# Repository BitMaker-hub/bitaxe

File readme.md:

# The Nerdaxe
NerdAxe is a fork from bitaxe with fullcolor display graphics. NerdAxe is indented to be an upgrade board for these who have a NerdMiner and would like to have more powerful mining features without losing the NerdMiner essence. That's why NerdAxe is currently controlled by the common board used on Nerdminer project called TTGO-TDisplayS3.

Currently exists two variants sepparated in two branches:
- **Nerdaxe Gamma**: 1,2Th with a single chip BM1370. [Nerdaxe Gamma](https://github.com/BitMaker-hub/NerdAxe/tree/gamma-1%2C2Ths)
- **Nerdaxe Ultra**: 0,5Th with a single chip BM1366. [Nerdaxe Ultra](https://github.com/BitMaker-hub/NerdAxe/tree/ultra-500Ghs)

The following fork could not be possible without the previous work of @skot, @ben & bitaxe devs. [Check bitaxe project](https://bitaxe.org)

Upgrade your NerdMiner experience throught this addon board and start playing with ASICs

## Goals
- **Plug&Play**: your NerdMiner board and convert it into a NerdAxe.
- **Standalone**: can mine directly to your pool over WiFi. No External computer needed.
- **Embedded**: low cost, low maintenance, high availability, high reliability, low power.
- **ASIC**: working with most efficient ASIC chips from Bitmain - BM1370.
- **Versatile**: solo/pool mining, autotune power/heat/efficiency.
- **Open Source**: All design files are provided.

## Features
- **TTGO-TDisplay** ESP32s3 wifi microcontroller display board
- **Multiple Screens** to allow you see all the miner stats 
- **TI TPS546D** buck regulator steps down the 5V input to power the BM1370
- **Microchip EMC2101** PWM controls the fan and monitors tach output. Measuring internal die temp isn't working.

## Software & Firmware
Nerdaxe firmware was forked from original ESP-Miner version and adapted to use TTGO board and LVGL as graphic interface lib. 
Check it here -> [ESP-Miner Nerdaxe version](https://github.com/BitMaker-hub/ESP-Miner-NerdAxe)

**Today** Nerdaxe is using the latest evolution of this firmware modified by @pmaxuw (creator of the NerdQaxe) and used for other multiple boards
Current firmware -> [ESP-Miner Nerd\*axe version](https://github.com/shufps/ESP-Miner-NerdQAxePlus)

Flash the latest Nerdaxe firmware here: 
- Go to flasher online tool: https://flasher.bitronics.store/ (recommend via Google Chrome incognito mode)
- Nerd\*axe flasher online tool: https://shufps.github.io/nerdqaxe-web-flasher/  

## The DIY area

### Asic BM1370
- The BM1370 is a undocumented SHA256 mining ASIC from Bitmain. It's mostly used in the Antminer S21pro/S21+
- Bitmain claims the BM1370 has 0.021J/GH efficiency
- The BM1370 is available (new) for around $60 each in small quantities.
- The BM1370 has a different footprint and pinout from the MB1366, BM1368 in previous bitaxe.

### Other components & build troubleshooting
- BM1370 from NBTC on AliExpress
- [40x40mm heatsink and 5V fan](https://www.aliexpress.com/item/2251832861666365.html) from a random AliExpress seller. At least half of these arrived broken in some way. But they are cheap and the working ones do keep the BM1387's nice and cool when used with some thermal compound.
    - Swap this fan with the [Noctua NF-A4x10](https://noctua.at/en/products/fan/nf-a4x10-pwm) 5V 4-Pin fan for a much more pleasant experience.
- Board is designed with [KiCad 8](https://www.kicad.org) design files
- All of the parts on the board are listed in the KiCad BOM
- Check out [building.md](building.md) for PCB ordering tips
- Check out [assembly.md](assembly.md) for assembly tips

### Power Supply Requirements
- 5VDC Power supply 5A minimum. Should be capable of over 25W

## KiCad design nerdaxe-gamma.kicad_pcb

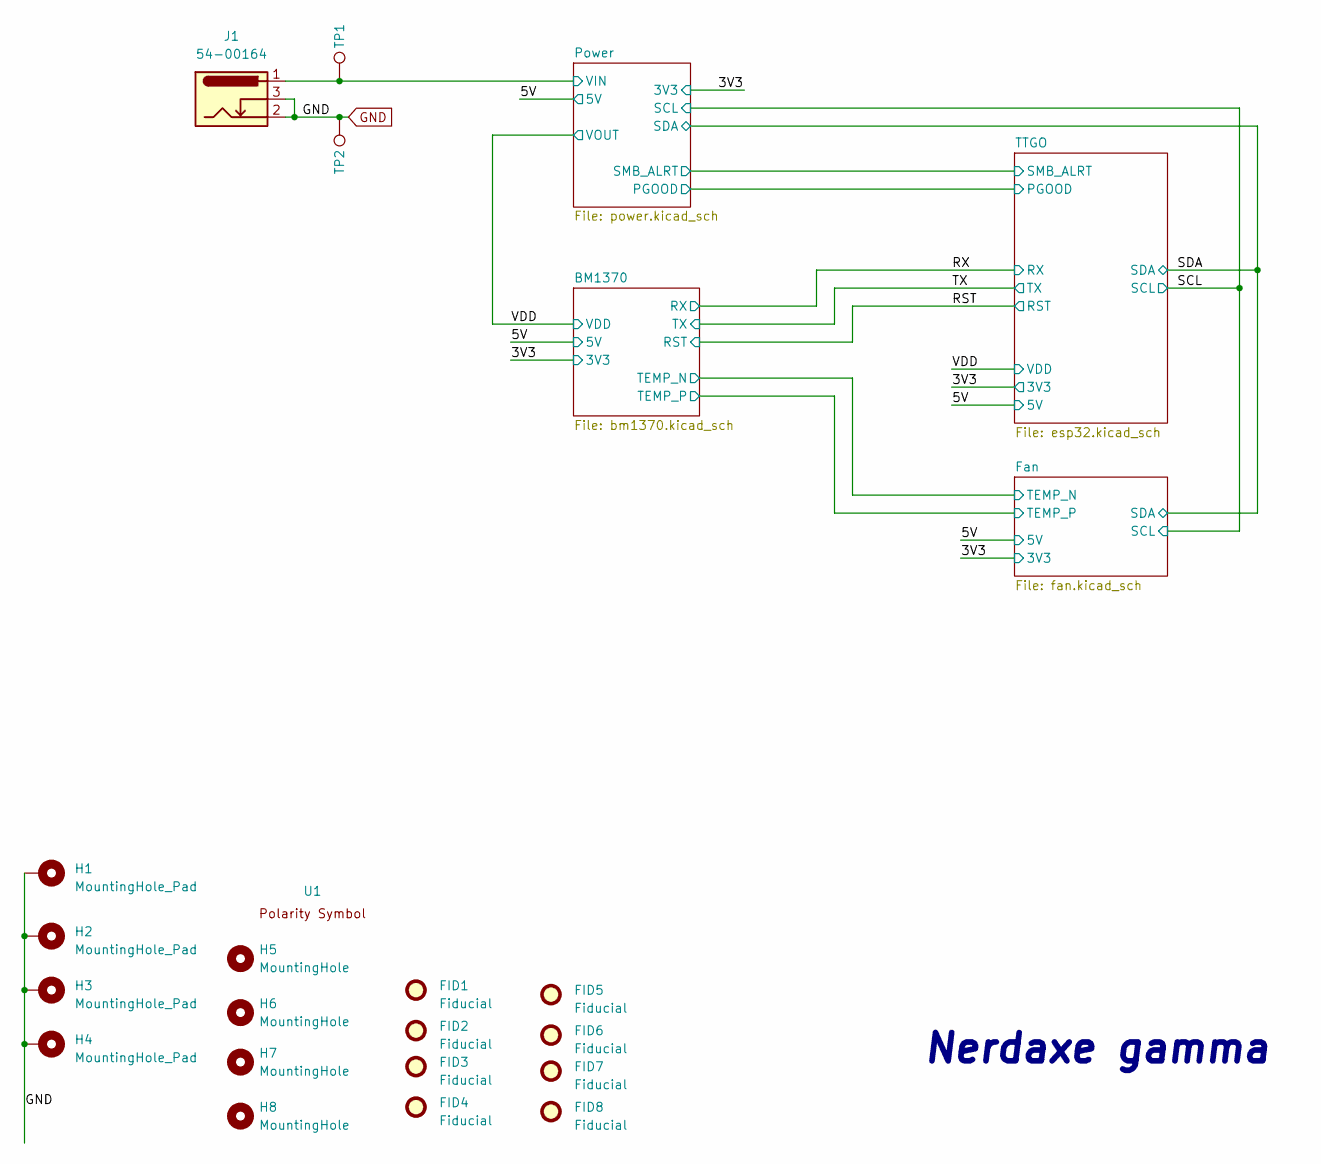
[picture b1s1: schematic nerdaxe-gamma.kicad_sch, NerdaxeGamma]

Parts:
FID1, FID2, FID3, FID4, FID5, FID6, FID7, FID8: Fiducial; Fiducial_1mm_Mask2mm
H1, H2, H3, H4: MountingHole_Pad; MountingHole_3mm_Pad_Via
H5, H6, H7, H8: MountingHole; MountingHole_3.5mm
J1: 54-00164; TENSILITY_54-00164; PARTNO 54-00164; LCSC C431534
TP1, TP2: TestPoint; TestPoint_Pad_D1.5mm
U1: polarity

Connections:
/5V: J1.1, TP1.1; also elsewhere on the board

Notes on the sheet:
Nerdaxe gamma

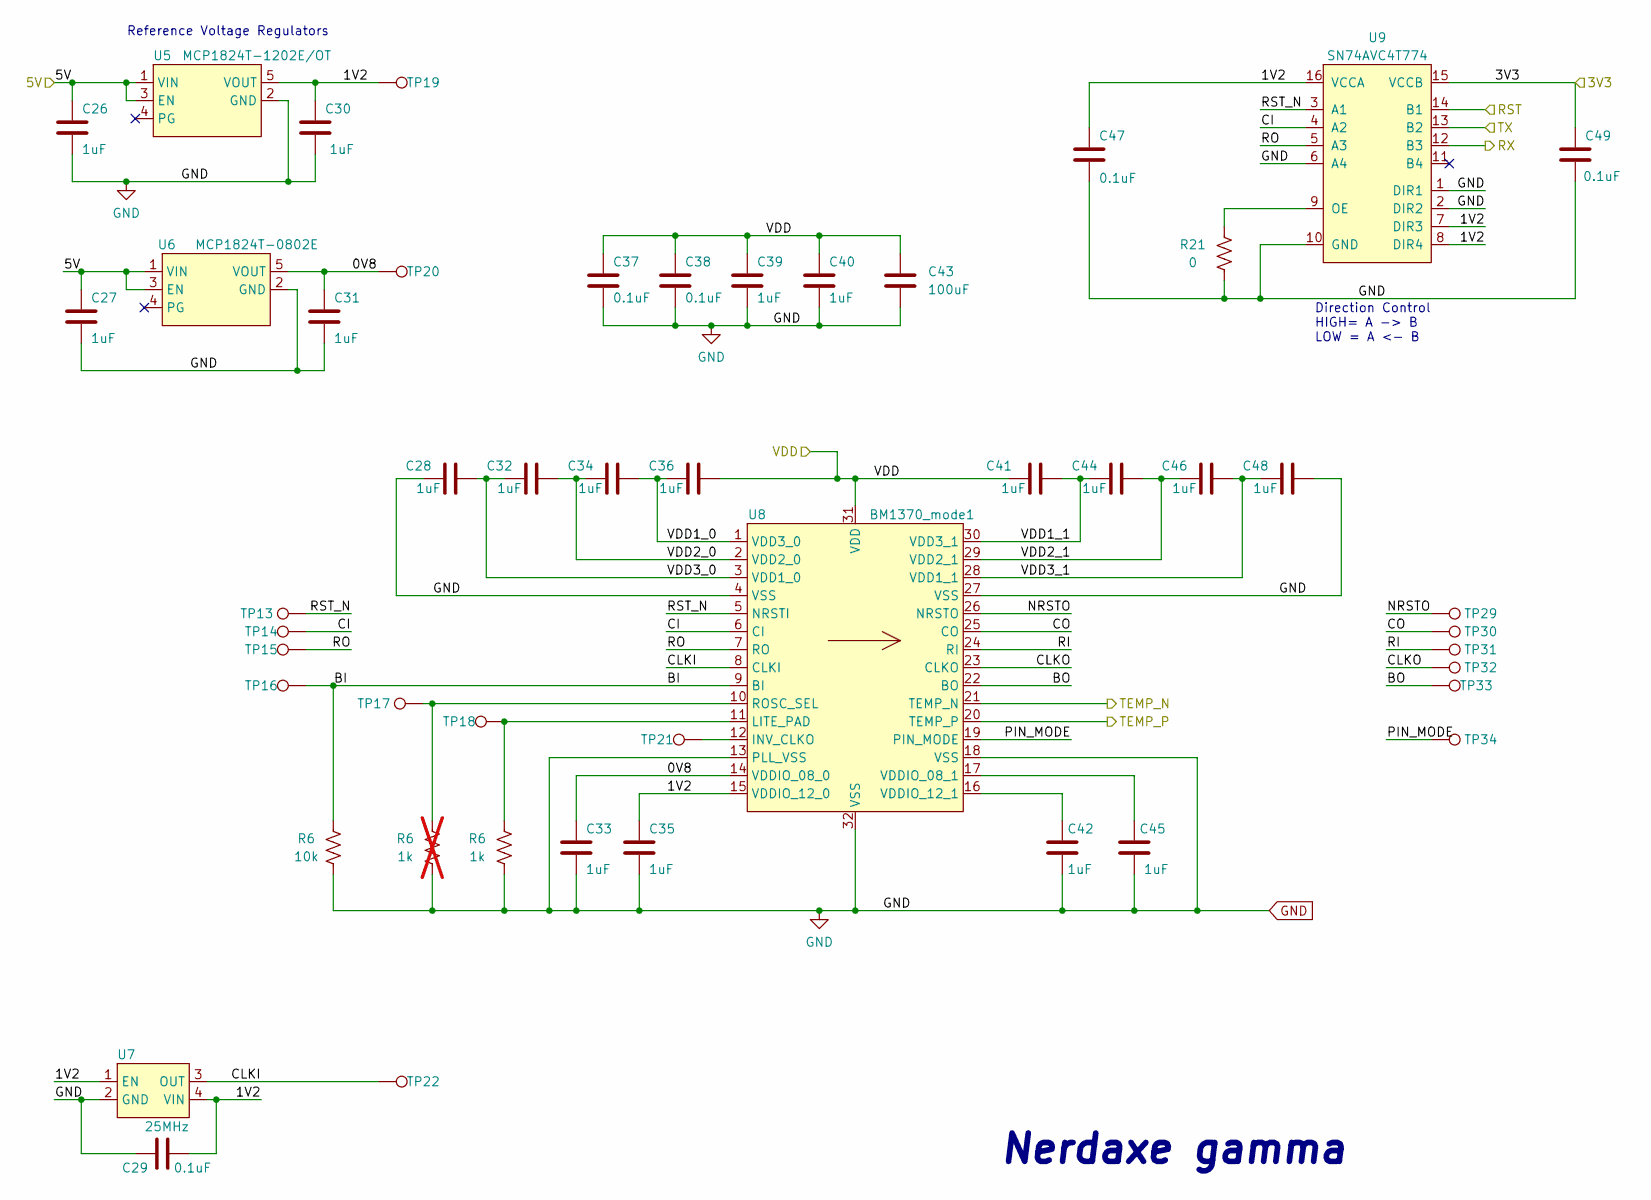
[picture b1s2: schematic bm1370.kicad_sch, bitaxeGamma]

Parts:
C26, C27, C28, C30, C31, C32, C33, C34, C35, C36, C39, C40, C41, C42, C44, C45, C46, C48: 1uF; C_0402_1005Metric; PARTNO EMK105BJ105MV-F
C29, C37, C38, C47, C49: 0.1uF; C_0402_1005Metric; PARTNO CL05A104KO5NNNC
C43: 100uF; C_1206_3216Metric; PARTNO CL31A107MQHNNNE
R6: 1k; R_0402_1005Metric; PARTNO RC0402FR-071KL; not fitted
R21: 0; R_0402_1005Metric; PARTNO RC0402FR-0720KL
TP13, TP14, TP15, TP16, TP17, TP18, TP19, TP20, TP21, TP22, TP29, TP30, TP31, TP32, TP33, TP34: TestPoint; TestPoint_Pad_D1.5mm
U5: MCP1824T-1202E/OT; SOT-23-5; PARTNO MCP1824T-1202E/OT
U6: MCP1824T-0802E; SOT-23-5; PARTNO MCP1824T-0802E/OT
U7: 25MHz; SMD3225-4P; PARTNO SX3M25.000E20F30THN; LCSC C5137262
U8: BM1370_mode1; BM1370
U9: SN74AVC4T774; TSSOP-16_4.4x5mm_P0.65mm; PARTNO SN74AVC4T774PWR

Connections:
/3V3: C49.1, U9.15 (VCCB); also elsewhere on the board
/5V: C26.1, C27.1, U5.1 (VIN), U5.3 (EN), U6.1 (VIN), U6.3 (EN); also elsewhere on the board
/BM1370/0V8: C31.1, C33.1, TP20.1, U6.5 (VOUT), U8.14 (VDDIO_08_0)
/BM1370/1V2: C29.2, C30.1, C35.1, C47.1, TP19.1, U5.5 (VOUT), U7.1 (EN), U7.4 (VIN), U8.15 (VDDIO_12_0), U9.7 (DIR3), U9.8 (DIR4), U9.16 (VCCA)
/BM1370/BO: TP33.1, U8.22 (BO)
/BM1370/CI: TP14.1, U8.6 (CI), U9.4 (A2)
/BM1370/CLKI: TP22.1, U7.3 (OUT), U8.8 (CLKI)
/BM1370/CLKO: TP32.1, U8.23 (CLKO)
/BM1370/CO: TP30.1, U8.25 (CO)
/BM1370/NRSTO: TP29.1, U8.26 (NRSTO)
/BM1370/PIN_MODE: TP34.1, U8.19 (PIN_MODE)
/BM1370/RI: TP31.1, U8.24 (RI)
/BM1370/RO: TP15.1, U8.7 (RO), U9.5 (A3)
/BM1370/RST_N: TP13.1, U8.5 (NRSTI), U9.3 (A1)
/BM1370/VDD1_0: C34.2, C36.1, U8.1 (VDD3_0)
/BM1370/VDD1_1: C41.2, C44.1, U8.30 (VDD3_1)
/BM1370/VDD2_0: C32.2, C34.1, U8.2 (VDD2_0)
/BM1370/VDD2_1: C44.2, C46.1, U8.29 (VDD2_1)
/BM1370/VDD3_0: C28.2, C32.1, U8.3 (VDD1_0)
/BM1370/VDD3_1: C46.2, C48.1, U8.28 (VDD1_1)
/Fan/TEMP_N: U8.21 (TEMP_N); also elsewhere on the board
/Fan/TEMP_P: U8.20 (TEMP_P); also elsewhere on the board
/RST: U9.14 (B1); also elsewhere on the board
/RX: U9.12 (B3); also elsewhere on the board
/TX: U9.13 (B2); also elsewhere on the board
/VDD: C36.2, C37.1, C38.1, C39.1, C40.1, C41.1, C43.1, U8.31 (VDD); also elsewhere on the board
unnamed: TP21.1, U8.12 (INV_CLKO)
unnamed: C45.1, U8.17 (VDDIO_08_1)
unnamed: C42.1, U8.16 (VDDIO_12_1)
unnamed: R21.2, U9.9 (OE)

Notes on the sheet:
Reference Voltage Regulators
Direction Control HIGH= A -> B LOW = A <- B
Nerdaxe gamma

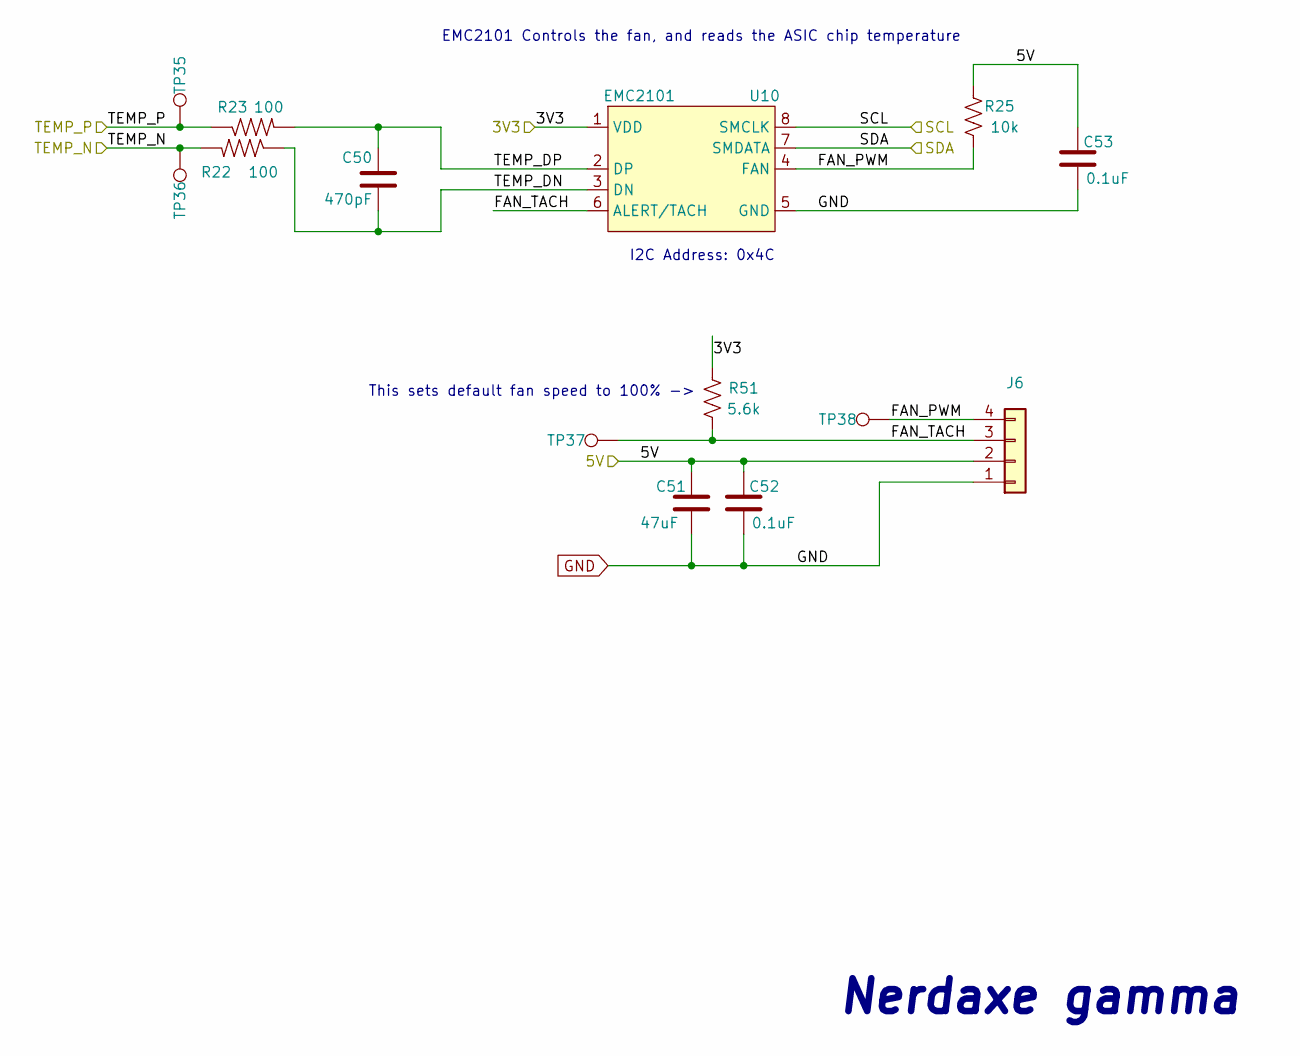
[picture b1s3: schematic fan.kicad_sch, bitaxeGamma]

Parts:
C50: 470pF; C_0402_1005Metric; PARTNO CL05B471KB5NNNC
C51: 47uF; C_1210_3225Metric; PARTNO CL32A476KOJNNNE
C52, C53: 0.1uF; C_0402_1005Metric; PARTNO CL05A104KO5NNNC
J6: Conn_01x04; 470531000; PARTNO 0470531000
R22, R23: 100; R_0402_1005Metric; PARTNO RC0402FR-07100RL
R25: 10k; R_0402_1005Metric; PARTNO RC0402JR-0710KL
R51: 5.6k; R_0402_1005Metric; PARTNO RC0402FR-135K6L
TP35, TP36, TP37, TP38: TestPoint; TestPoint_Pad_D1.5mm
U10: EMC2101; TSSOP-8_3x3mm_P0.65mm; PARTNO EMC2101-R-ACZL-TR

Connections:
/3V3: U10.1 (VDD); also elsewhere on the board
/5V: C51.1, C52.1, C53.1, J6.2, R25.2; also elsewhere on the board
/Fan/FAN_PWM: J6.4, R25.1, TP38.1, U10.4 (FAN)
/Fan/FAN_TACH: J6.3, TP37.1, U10.6 (ALERT/TACH); also elsewhere on the board
/Fan/TEMP_DN: C50.2, R22.1, U10.3 (DN)
/Fan/TEMP_DP: C50.1, R23.2, U10.2 (DP)
/Fan/TEMP_N: R22.2, TP36.1; also elsewhere on the board
/Fan/TEMP_P: R23.1, TP35.1; also elsewhere on the board
/SCL: U10.8 (SMCLK); also elsewhere on the board
/SDA: U10.7 (SMDATA); also elsewhere on the board

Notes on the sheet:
Nerdaxe gamma
EMC2101 Controls the fan, and reads the ASIC chip temperature
This sets default fan speed to 100% ->
I2C Address: 0x4C

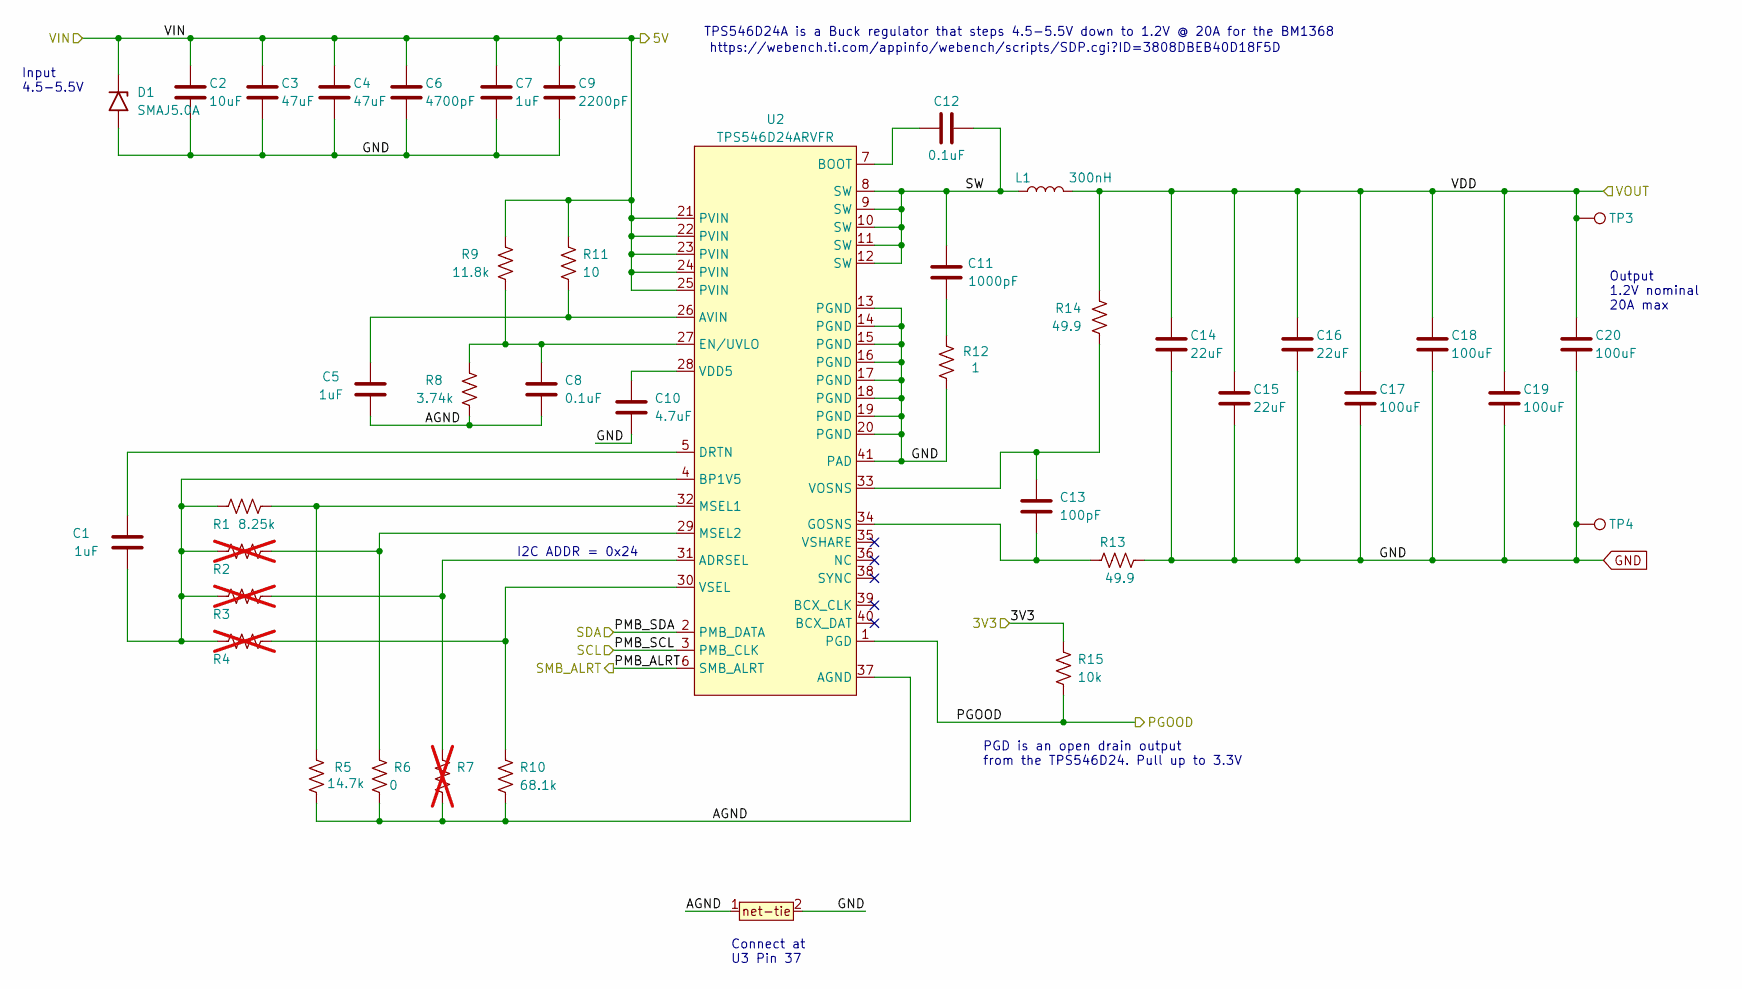
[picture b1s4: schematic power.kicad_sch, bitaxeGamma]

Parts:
C1, C5, C7: 1uF; C_0402_1005Metric; PARTNO EMK105BJ105MV-F
C2: 10uF; C_0805_2012Metric; PARTNO CL21A106KOQNNNE
C3, C4: 47uF; C_1210_3225Metric; PARTNO CL32A476KOJNNNE
C6: 4700pF; C_0402_1005Metric; PARTNO GRM155R71E472KA01D
C8, C12: 0.1uF; C_0402_1005Metric; PARTNO CL05A104KO5NNNC
C9: 2200pF; C_0402_1005Metric; PARTNO GRM155R61H222KA01D
C10: 4.7uF; C_0402_1005Metric; PARTNO GRM155R61A475MEAAD
C11: 1000pF; C_0805_2012Metric; PARTNO CC0805KRX7R9BB102
C13: 100pF; C_0402_1005Metric; PARTNO 885012005013
C14, C15, C16: 22uF; C_0805_2012Metric; PARTNO GRM21BR61A226ME44L
C17, C18, C19, C20: 100uF; C_1206_3216Metric; PARTNO CL31A107MQHNNNE
D1: SMAJ5.0A; D_SMA
L1: 300nH; SLC1175-271MEC_COC; PARTNO SLC1175-301MEC; Mouser 994-SLC1175-271MEC
R1: 8.25k; R_0402_1005Metric; PARTNO RC0402FR-078K25L
R2, R3, R4, R7: R_0402_1005Metric; not fitted
R5: 14.7k; R_0402_1005Metric; PARTNO RC0402FR-0714K7L
R6: 0; R_0402_1005Metric; PARTNO RC0402JR-070RL
R8: 3.74k; R_0402_1005Metric; PARTNO RC0402FR-073K74L
R9: 11.8k; R_0402_1005Metric; PARTNO RC0402FR-0711K8L
R10: 68.1k; R_0402_1005Metric; PARTNO RC0402FR-0768K1L
R11: 10; R_0402_1005Metric; PARTNO RC0402FR-0710RL
R12: 1; R_1206_3216Metric; PARTNO CSR1206FT1R00
R13, R14: 49.9; R_0402_1005Metric; PARTNO RC0402FR-0749R9L
R15: 10k; R_0402_1005Metric; PARTNO RC0402JR-0710KL
T1: net-tie; NetTie-0.25mm
TP3, TP4: TestPoint; TestPoint_Pad_D1.5mm
U2: TPS546D24ARVFR; LQFN40-CLIP; PARTNO TPS546D24ARVFR

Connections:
/3V3: R15.2; also elsewhere on the board
/5V: C2.1, C3.1, C4.1, C6.1, C7.1, C9.1, D1.1 (A1), R9.1, R11.1, U2.21 (PVIN), U2.22 (PVIN), U2.23 (PVIN), U2.24 (PVIN), U2.25 (PVIN); also elsewhere on the board
/Power/PGOOD: R15.1, U2.1 (PGD); also elsewhere on the board
/Power/PMB_ALRT: U2.6 (SMB_ALRT); also elsewhere on the board
/Power/SW: C11.2, C12.2, L1.1, U2.8 (SW), U2.9 (SW), U2.10 (SW), U2.11 (SW), U2.12 (SW)
/SCL: U2.3 (PMB_CLK); also elsewhere on the board
/SDA: U2.2 (PMB_DATA); also elsewhere on the board
/VDD: C14.1, C15.1, C16.1, C17.1, C18.1, C19.1, C20.1, L1.2, R14.1, TP3.1; also elsewhere on the board
unnamed: C11.1, R12.2
unnamed: R3.2, R7.1, U2.31 (ADRSEL)
unnamed: C5.2, R11.2, U2.26 (AVIN)
unnamed: C12.1, U2.7 (BOOT)
unnamed: C1.2, R1.1, R2.1, R3.1, R4.1, U2.4 (BP1V5)
unnamed: C1.1, U2.5 (DRTN)
unnamed: C8.1, R8.1, R9.2, U2.27 (EN/UVLO)
unnamed: C13.2, R13.1, U2.34 (GOSNS)
unnamed: R1.2, R5.2, U2.32 (MSEL1)
unnamed: C10.1, U2.28 (VDD5)
unnamed: C13.1, R14.2, U2.33 (VOSNS)
unnamed: R4.2, R10.1, U2.30 (VSEL)

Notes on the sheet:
TPS546D24A is a Buck regulator that steps 4.5-5.5V down to 1.2V @ 20A for the BM1368
https://webench.ti.com/appinfo/webench/scripts/SDP.cgi?ID=3808DBEB40D18F5D
Input 4.5-5.5V
PGD is an open drain output from the TPS546D24. Pull up to 3.3V
I2C ADDR = 0x24
Output 1.2V nominal 20A max
Connect at U3 Pin 37

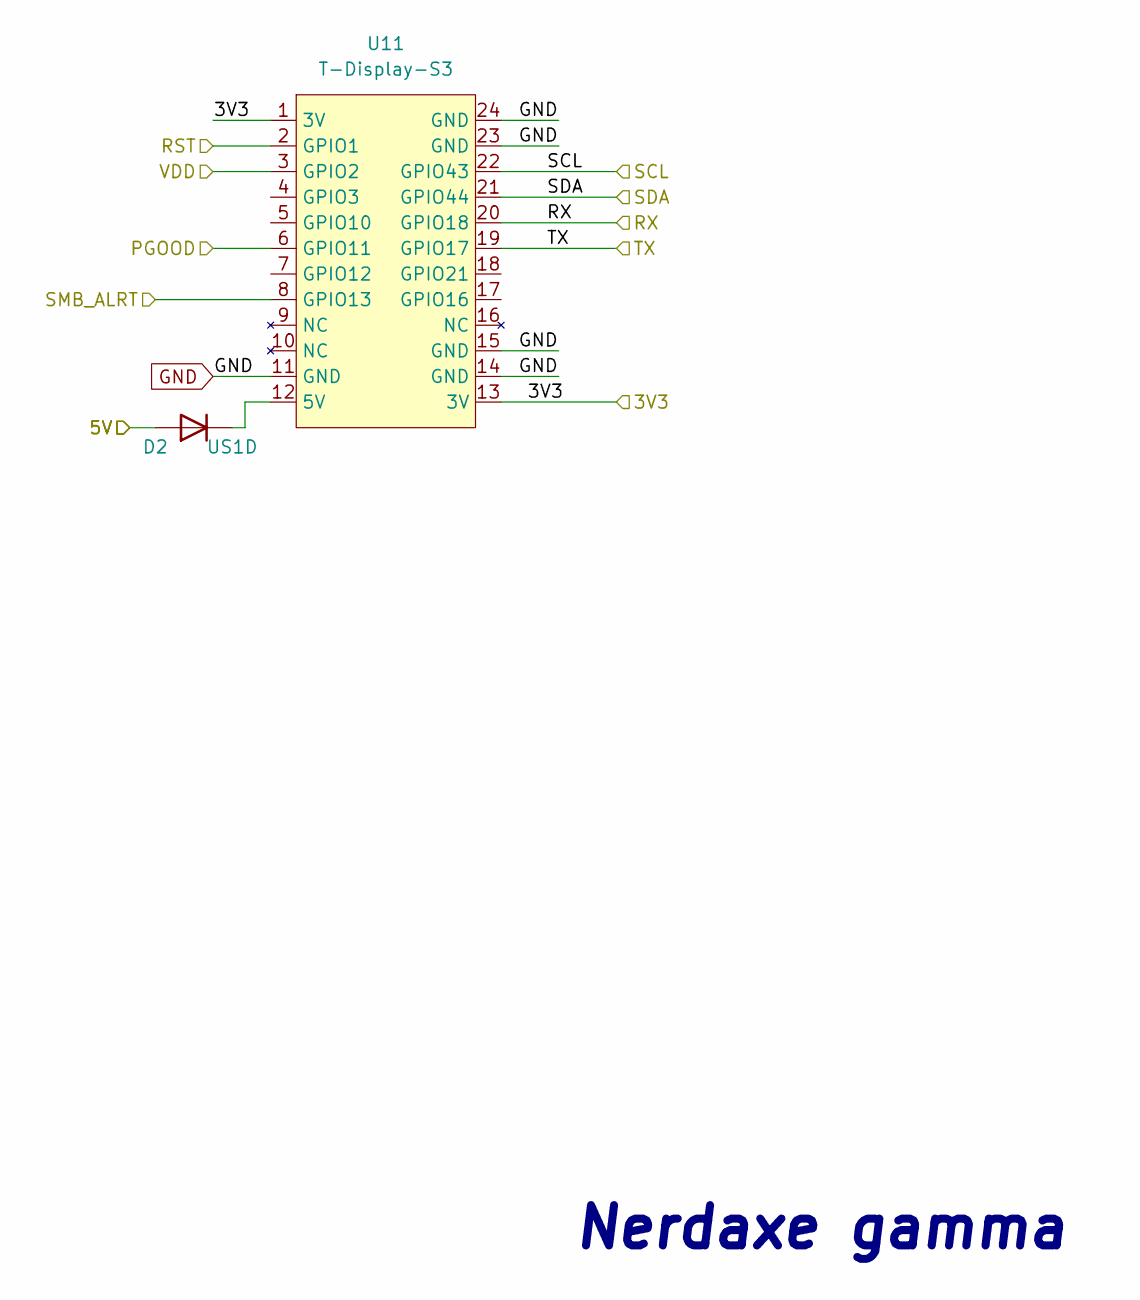
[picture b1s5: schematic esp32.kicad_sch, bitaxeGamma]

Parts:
D2: US1D; D_SMA
U11: T-Display-S3

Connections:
/3V3: U11.1 (3V), U11.13 (3V); also elsewhere on the board
/5V: D2.2 (A); also elsewhere on the board
/Power/PGOOD: U11.6 (GPIO11); also elsewhere on the board
/Power/PMB_ALRT: U11.8 (GPIO13); also elsewhere on the board
/RST: U11.2 (GPIO1); also elsewhere on the board
/RX: U11.20 (GPIO18); also elsewhere on the board
/SCL: U11.22 (GPIO43); also elsewhere on the board
/SDA: U11.21 (GPIO44); also elsewhere on the board
/TX: U11.19 (GPIO17); also elsewhere on the board
/VDD: U11.3 (GPIO2); also elsewhere on the board
unnamed: D2.1 (K), U11.12 (5V)

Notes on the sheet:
Nerdaxe gamma

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
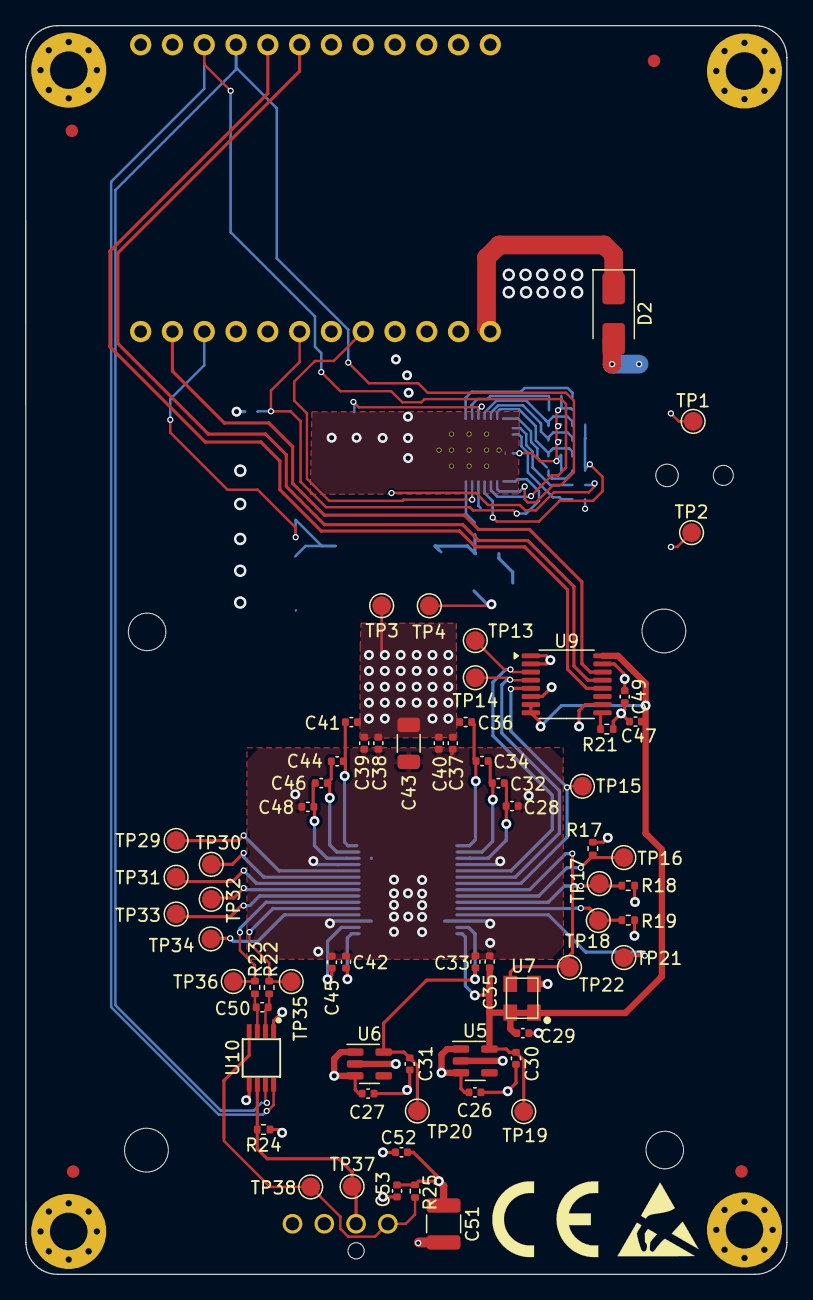
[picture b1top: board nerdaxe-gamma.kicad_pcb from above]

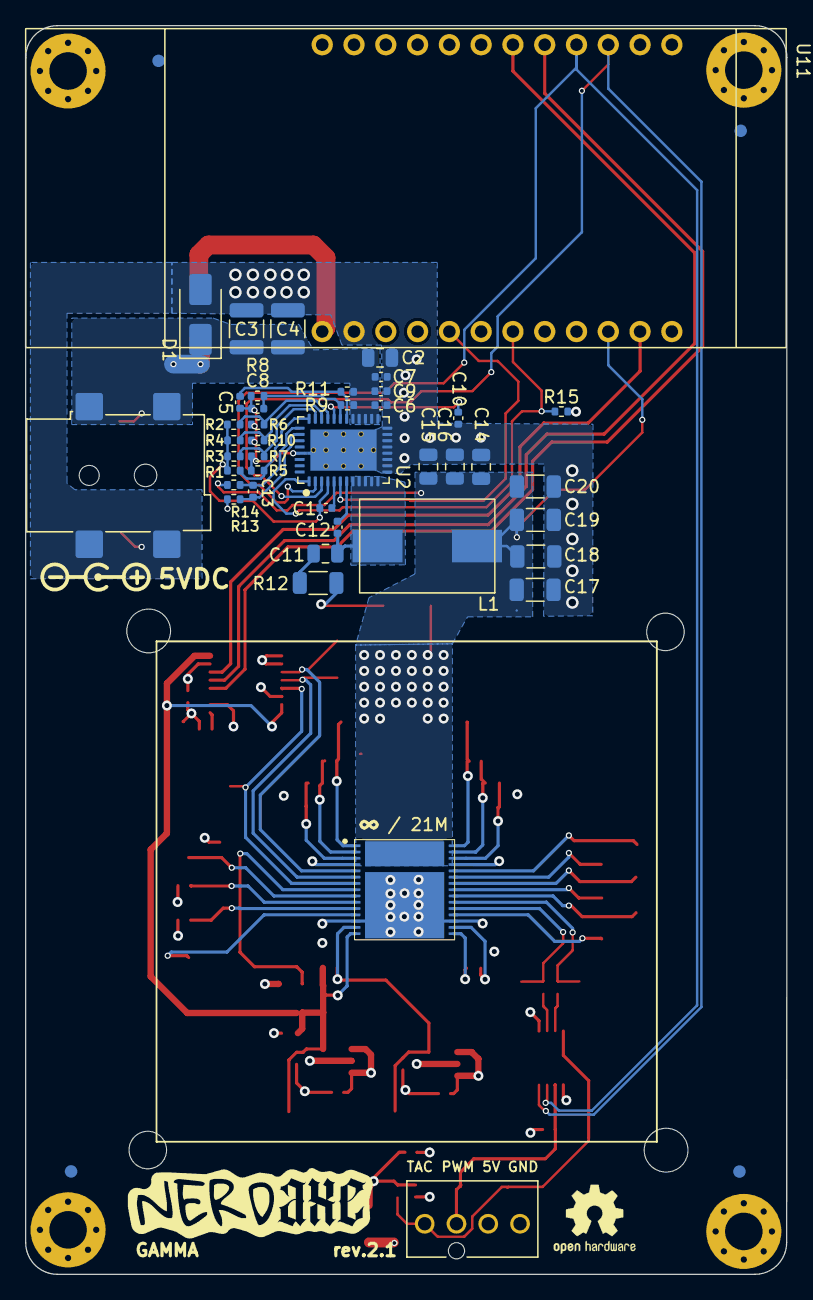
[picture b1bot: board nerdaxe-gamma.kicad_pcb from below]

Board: 4 copper layers, 60.8 x 99.8 mm, 126 parts (48 on the bottom side), 58 nets.

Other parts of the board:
R17: 10k; R_0402_1005Metric
R18, R19: 1k; R_0402_1005Metric
R24: 5.6k; R_0402_1005Metric

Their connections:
/3V3: R24.2; also elsewhere on the board
/Fan/FAN_TACH: R24.1; also elsewhere on the board

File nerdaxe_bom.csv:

Qty,Reference,Value,Footprint,DK,LCSC,Description
1,C2,10uF,Capacitor_SMD:C_0805_2012Metric,1276-1096-1-ND,,
1,C6,4700pF,Capacitor_SMD:C_0402_1005Metric,490-1309-1-ND,,
1,C9,2200pF,Capacitor_SMD:C_0402_1005Metric,490-8257-1-ND,,
1,C10,4.7uF,Capacitor_SMD:C_0402_1005Metric,490-14306-1-ND,,
1,C11,1000pF,Capacitor_SMD:C_0805_2012Metric,311-1127-1-ND,,
1,C13,100pF,Capacitor_SMD:C_0402_1005Metric,732-7431-1-ND,,
1,C50,470pF,Capacitor_SMD:C_0402_1005Metric,1276-1566-1-ND,,
21,C1 C5 C7 C26 C27 C28 C30 C31 C32 C33 C34 C35 C36 C39 C40 C41 C42 C44 C45 C46 C48,1uF,Capacitor_SMD:C_0402_1005Metric,587-5514-1-ND,,
3,C14 C15 C16,22uF,Capacitor_SMD:C_0805_2012Metric,490-10746-1-ND,,
5,C17 C18 C19 C20 C43,100uF,Capacitor_SMD:C_1206_3216Metric,1276-1782-1-ND,,-- valores mixtos --
3,C3 C4 C51,47uF,Capacitor_SMD:C_1210_3225Metric,1276-3376-1-ND,,
9,C8 C12 C29 C37 C38 C47 C49 C52 C53,0.1uF,Capacitor_SMD:C_0402_1005Metric,1276-1234-1-ND,,
1,D1,SMAJ5.0A,Diode_SMD:D_SMA,,,400W unidirectional Transient Voltage Suppressor, 5.0Vr, SMA(DO-214AC)
1,J1,54-00164,bitaxe:TENSILITY_54-00164,839-54-00164CT-ND,C431534,DC Barrel Jack with an internal switch
1,J6,Conn_01x04,bitaxe:470531000,WM4330-ND,,
1,L1,300nH,bitaxe:SLC1175-271MEC_COC,,,
1,R1,8.25k,Resistor_SMD:R_0402_1005Metric,311-8.25KLRCT-ND,,
1,R5,14.7k,Resistor_SMD:R_0402_1005Metric,YAG2984CT-ND,,
1,R8,3.74k,Resistor_SMD:R_0402_1005Metric,311-3.74KLRCT-ND,,
1,R9,11.8k,Resistor_SMD:R_0402_1005Metric,YAG2958CT-ND,,
1,R10,68.1k,Resistor_SMD:R_0402_1005Metric,YAG3213CT-ND,,
1,R11,10,Resistor_SMD:R_0402_1005Metric,311-10.0LRCT-ND,,
1,R12,1,Resistor_SMD:R_1206_3216Metric,CSR1206FT1R00CT-ND,,
1,R24,5.6k,Resistor_SMD:R_0402_1005Metric,13-RC0402FR-135K6LCT-ND,,
2,R13 R14,49.9,Resistor_SMD:R_0402_1005Metric,311-49.9LRCT-ND,,
3,R15 R17 R25,10k,Resistor_SMD:R_0402_1005Metric,311-10KJRCT-ND,,
2,R18 R19,1k,Resistor_SMD:R_0402_1005Metric,311-1.00KLRCT-ND,,
2,R22 R23,100,Resistor_SMD:R_0402_1005Metric,311-100LRCT-ND,,
2,R6 R21,0,Resistor_SMD:R_0402_1005Metric,-- valores mixtos --,,
1,U2,TPS546D24ARVFR,bitaxe:LQFN40-CLIP,296-TPS546D24ARVFRCT-ND,,
1,U5,MCP1824T-1202E/OT,Package_TO_SOT_SMD:SOT-23-5,MCP1824T-1202E/OTCT-ND,,
1,U6,MCP1824T-0802E,Package_TO_SOT_SMD:SOT-23-5,MCP1824T-0802E/OTCT-ND,,
1,U7,25MHz,bitaxe:SMD3225-4P,,C5137262,
1,U8,BM1370_mode1,bitaxe:BM1370,,,
1,U9,SN74AVC4T774,Package_SO:TSSOP-16_4.4x5mm_P0.65mm,296-24739-1-ND,,
1,U10,EMC2101,Package_SO:TSSOP-8_3x3mm_P0.65mm,EMC2101-R-ACZL-CT-ND,,
1,U11,T-Display-S3,bitaxe:T-Display-S3,,,

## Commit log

2025-02-06 Nerdaxe Gamma
2025-02-06 add repo images
2025-02-06 readme update
2025-02-06 readme fix
2025-02-06 flasher url fix
